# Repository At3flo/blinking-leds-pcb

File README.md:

# blinking-leds-pcb

Is a project ralized initially for the Numerik Games 2017

Initially it was supposed to be used on shoes with iluminated laces

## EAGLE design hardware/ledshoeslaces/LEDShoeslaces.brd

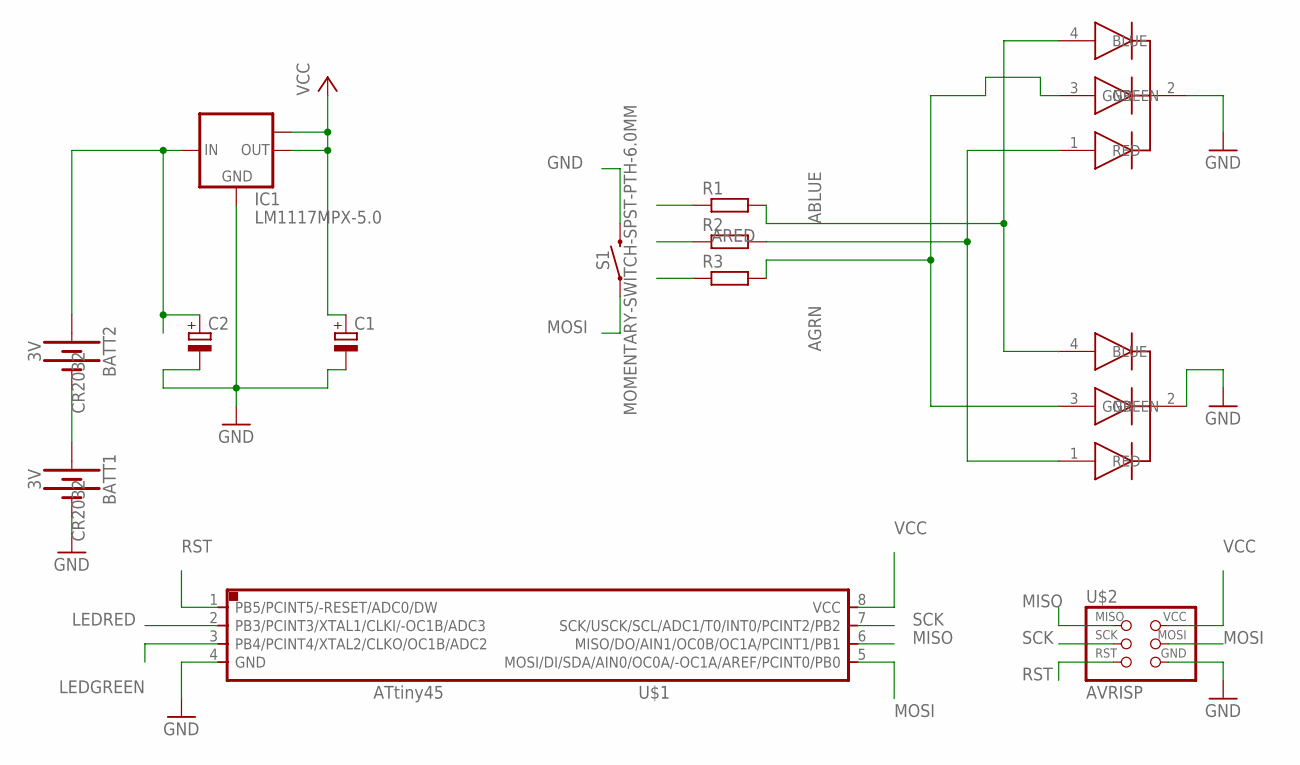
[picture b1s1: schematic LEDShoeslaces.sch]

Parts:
BATT1, BATT2: 3V; BATTCON_20MM
C1, C2: CPOL-EUCT7343; CT7343
IC1: LM1117MPX-5.0; SOT223
R1, R2, R3: R-EU_R1206; R1206
S1: MOMENTARY-SWITCH-SPST-PTH-6.0MM; TACTILE_SWITCH_PTH_6.0MM
U$1: ATTINY45SI; SOIC8
U$2: AVRISP; 2X03
U$3, U$4: LEDRGB

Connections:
ABLUE: R1.2, U$3.4 (BLUE), U$4.4 (BLUE)
AGRN: R3.2, U$3.3 (GREEN), U$4.3 (GREEN)
ARED: R2.2, U$3.1 (RED), U$4.1 (RED)
BATS: BATT1.1 (+), BATT2.2 (-)
GND: BATT1.2 (-), C1.-, C2.-, IC1.1 (GND), S1.3 (2), U$1.4 (GND), U$2.6 (GND), U$3.2 (GND), U$4.2 (GND)
LEDGREEN: R3.1, U$1.3 (PB4/PCINT4/XTAL2/CLKO/OC1B/ADC2)
LEDRED: R1.1, U$1.2 (PB3/PCINT3/XTAL1/CLKI/-OC1B/ADC3)
MISO: R2.1, U$1.6 (MISO/DO/AIN1/OC0B/OC1A/PCINT1/PB1), U$2.1 (MISO)
MOSI: S1.1, U$1.5 (MOSI/DI/SDA/AIN0/OC0A/-OC1A/AREF/PCINT0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), U$2.4 (MOSI)
RST: U$1.1 (PB5/PCINT5/-RESET/ADC0/DW), U$2.5 (RST)
SCK: U$1.7 (SCK/USCK/SCL/ADC1/T0/INT0/PCINT2/PB2), U$2.3 (SCK)
VCC: C1.+, IC1.2 (OUT), IC1.TAB (OUT1), U$1.8 (VCC), U$2.2 (VCC)
V_BATT: BATT2.1 (+), C2.+, IC1.3 (IN)

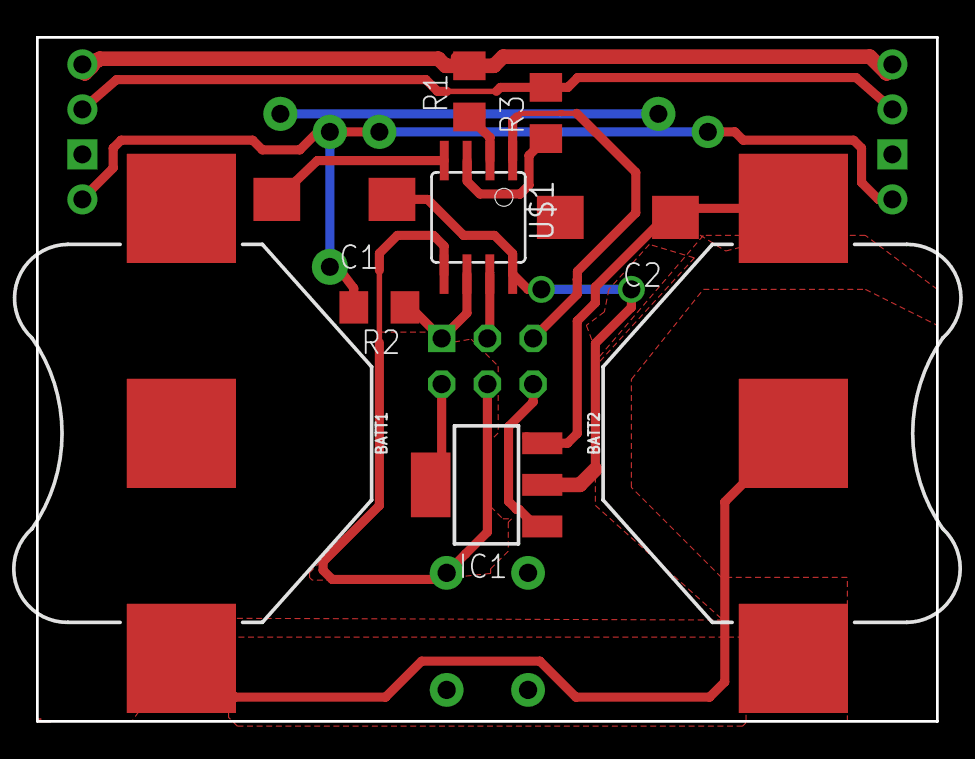
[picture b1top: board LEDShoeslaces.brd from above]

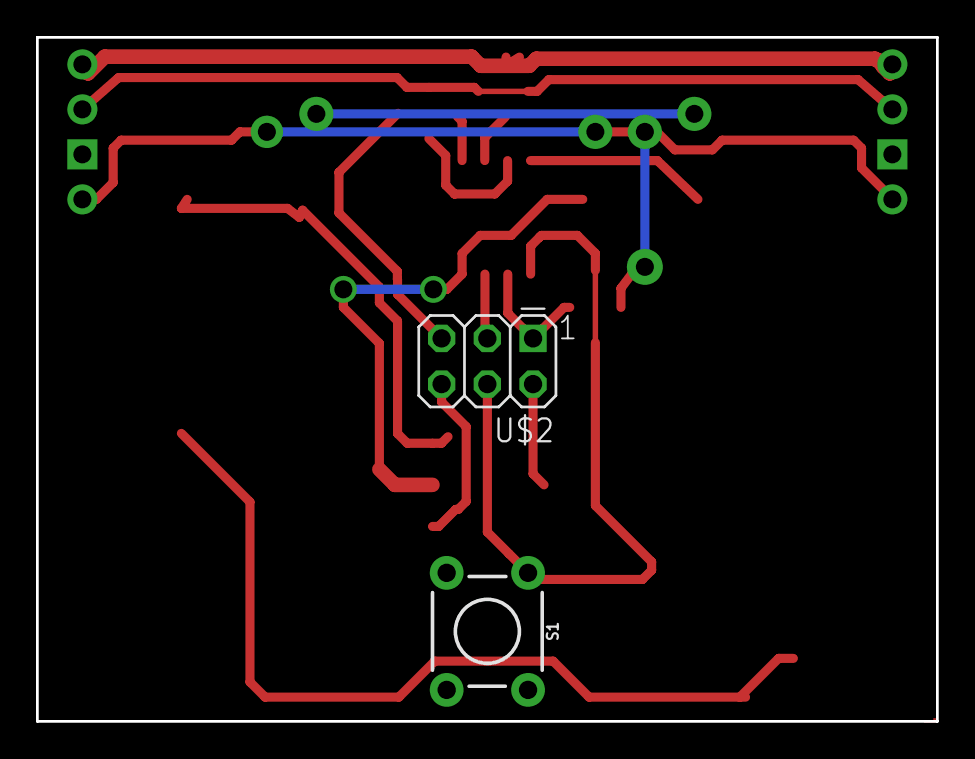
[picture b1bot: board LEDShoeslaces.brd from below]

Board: 2 copper layers, 50.0 x 38.0 mm, 13 parts (2 on the bottom side), 13 nets.

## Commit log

2017-08-23 initial import
2017-08-23 3 mode usable, need to add EEPROM features
2017-08-24 fix unconnected
2017-08-24 prepare etching
2017-08-24 Added assets folder with img
2017-08-24 fix spacings
2017-08-24 fix minor issues viewed on printed
2017-08-24 Created a PDF mask for 2 PCBs + added A3O DXF Logo
2017-08-25 fixing bad led pad
2017-08-25 zzZZzZZZzzz
2017-08-25 Added pocket for speed manufacturing
2017-08-25 Export design to PNG 1200dpi
2017-08-25 Added traces PNG, SVG, etc.
2017-08-25 rasnet fix cc with ground
2017-08-25 Added 1st GCode + Laser parameters + laser img
2017-08-25 Reproduced PNG/SVG files
2017-08-25 RDWorks file
2017-08-25 Corrected the right pad under BAT2
2017-08-26 Small changes in Laser process
2017-08-26 fix button....
2017-08-26 Added Adam Seychelles Method to etching
2017-08-26 led pad size
2017-08-26 Reorder all the files + regenerate PNGs + laser files
2017-08-27 working version

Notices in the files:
parts and their libraries:
SparkFun-Batteries: Licensing: Creative Commons ShareAlike 4.0 International - https://creativecommons.org/licenses/by-sa/4.0
